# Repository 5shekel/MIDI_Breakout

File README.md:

MIDI In/Out/Thru For stuff
========================================

NOTE: work in progress, this should work but still unetched ...  
NOTE2: SF has V_1.2 [[0]](https://github.com/sparkfun/MIDI_Breakout/tree/V_1.2) branch (work in progress) with an added line driver [[1]](http://www.nxp.com/documents/data_sheet/74AHC_AHCT1G125.pdf) for MIDI_OUT and MIDI_THRU.    
common lore on the internet tells its unesscery, midi can survivie hundered of meters without [[2]](https://groups.google.com/forum/#!topic/theatre-sound-list/aL6dRYNXyxQ) [[3](http://www.richmondsounddesign.com/faq.html#midilen).  

SF design suffers from a few problems, like   
* the PROG/RUN jumper : non here, connect your micro to software serial. or whatever  
* the uno formfactor: we are over(under) it, design is for ruggedness  
* 0402 footprint - no need for the tiniest parts. we use thru hole a lot here beaucse anyways the midi sockets are big.  
  
this is a fork, you know

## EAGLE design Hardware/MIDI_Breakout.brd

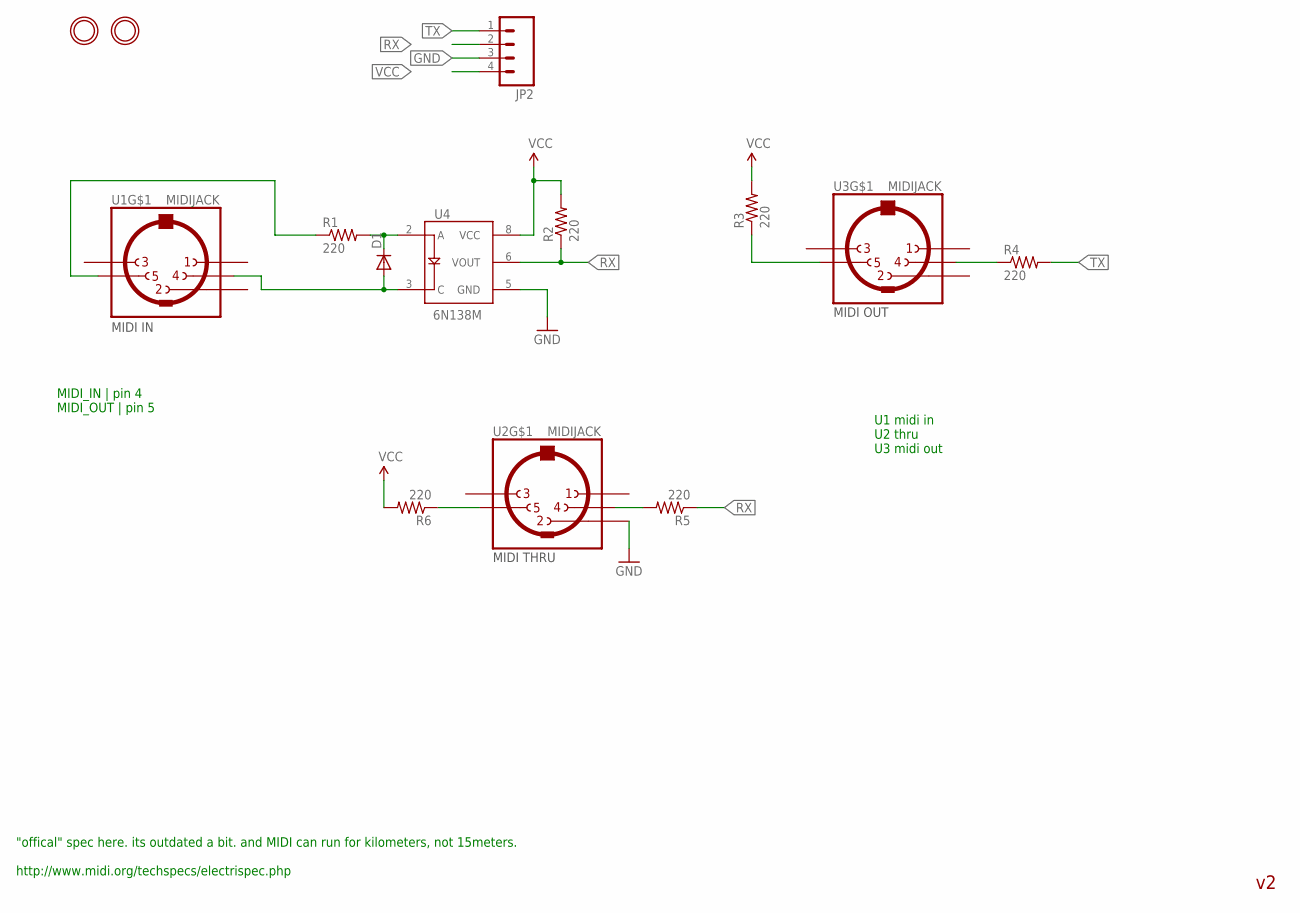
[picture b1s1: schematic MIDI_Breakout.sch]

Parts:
D1: DIODESMA; SMA-DIODE
JP2: M041X04_NO_SILK; 1X04_NO_SILK
R1, R2, R3, R4, R5, R6: 220; AXIAL-0.5
U1, U2, U3: MIDIJACK; CP-2350
U4: 6N138M; 8-SMD
U$1, U$2: MOUNTINGHOLE; MOUNTINGHOLE_3.0_PLATED

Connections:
56: D1.C, R1.P$2 (2), U4.2 (A)
1235: R3.P$1 (1), U3.5
GND: JP2.3, U2.2, U4.5 (GND)
unnamed: R6.P$1 (1), U2.5
unnamed: R5.P$2 (2), U2.4
unnamed: R1.P$1 (1), U1.5
unnamed: R4.P$1 (1), U3.4
PIN5: D1.A, U1.4, U4.3 (C)
RX: JP2.2, R2.P$1 (1), R5.P$1 (1), U4.6 (VOUT)
TX: JP2.1, R4.P$2 (2)
VCC: JP2.4, R2.P$2 (2), R3.P$2 (2), R6.P$2 (2), U4.8 (VCC)

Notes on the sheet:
MIDI IN
MIDI OUT
MIDI THRU
MIDI_IN | pin 4 MIDI_OUT | pin 5
U1 midi in U2 thru U3 midi out
"offical" spec here. its outdated a bit. and MIDI can run for kilometers, not 15meters. http://www.midi.org/techspecs/electrispec.php

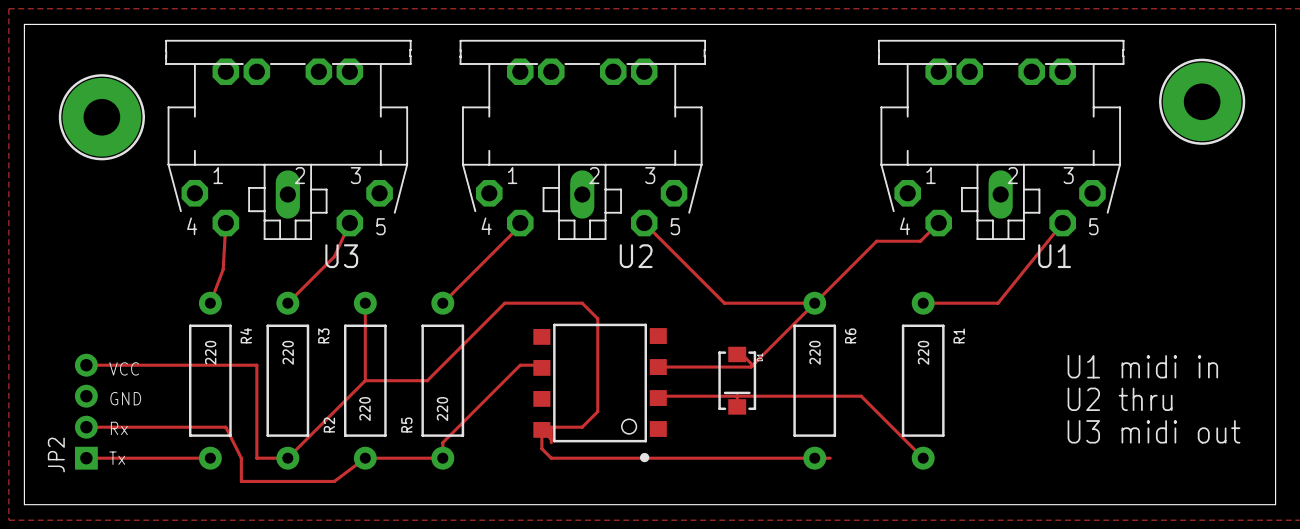
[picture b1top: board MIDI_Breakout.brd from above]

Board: 2 copper layers, 102.5 x 39.4 mm, 14 parts (0 on the bottom side), 11 nets.

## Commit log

2015-06-01 changed form factor, removed UNO pads, no more prog mode
2015-06-01 mix thru hole and smd, layoutmostly
2015-06-02 Update README.md
    add pic
2015-06-02 Update README.md
    schematic pic
2015-06-02 Update README.md
    change schematic
2015-06-02 Update README.md
    warning WIP
2015-06-02 Update README.md
    v1.2 toughts

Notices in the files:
parts and their libraries:
SparkFun-DiscreteSemi: Licensing: Creative Commons ShareAlike 4.0 International - https://creativecommons.org/licenses/by-sa/4.0
microbuilder: This work is placed in the public domain, and may be freely used for commercial and non-commercial work with the following conditions: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
